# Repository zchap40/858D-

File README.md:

# 858E
(Otherwise known as the 858D++)
A new design for a hot air soldering station based on the original 858D+

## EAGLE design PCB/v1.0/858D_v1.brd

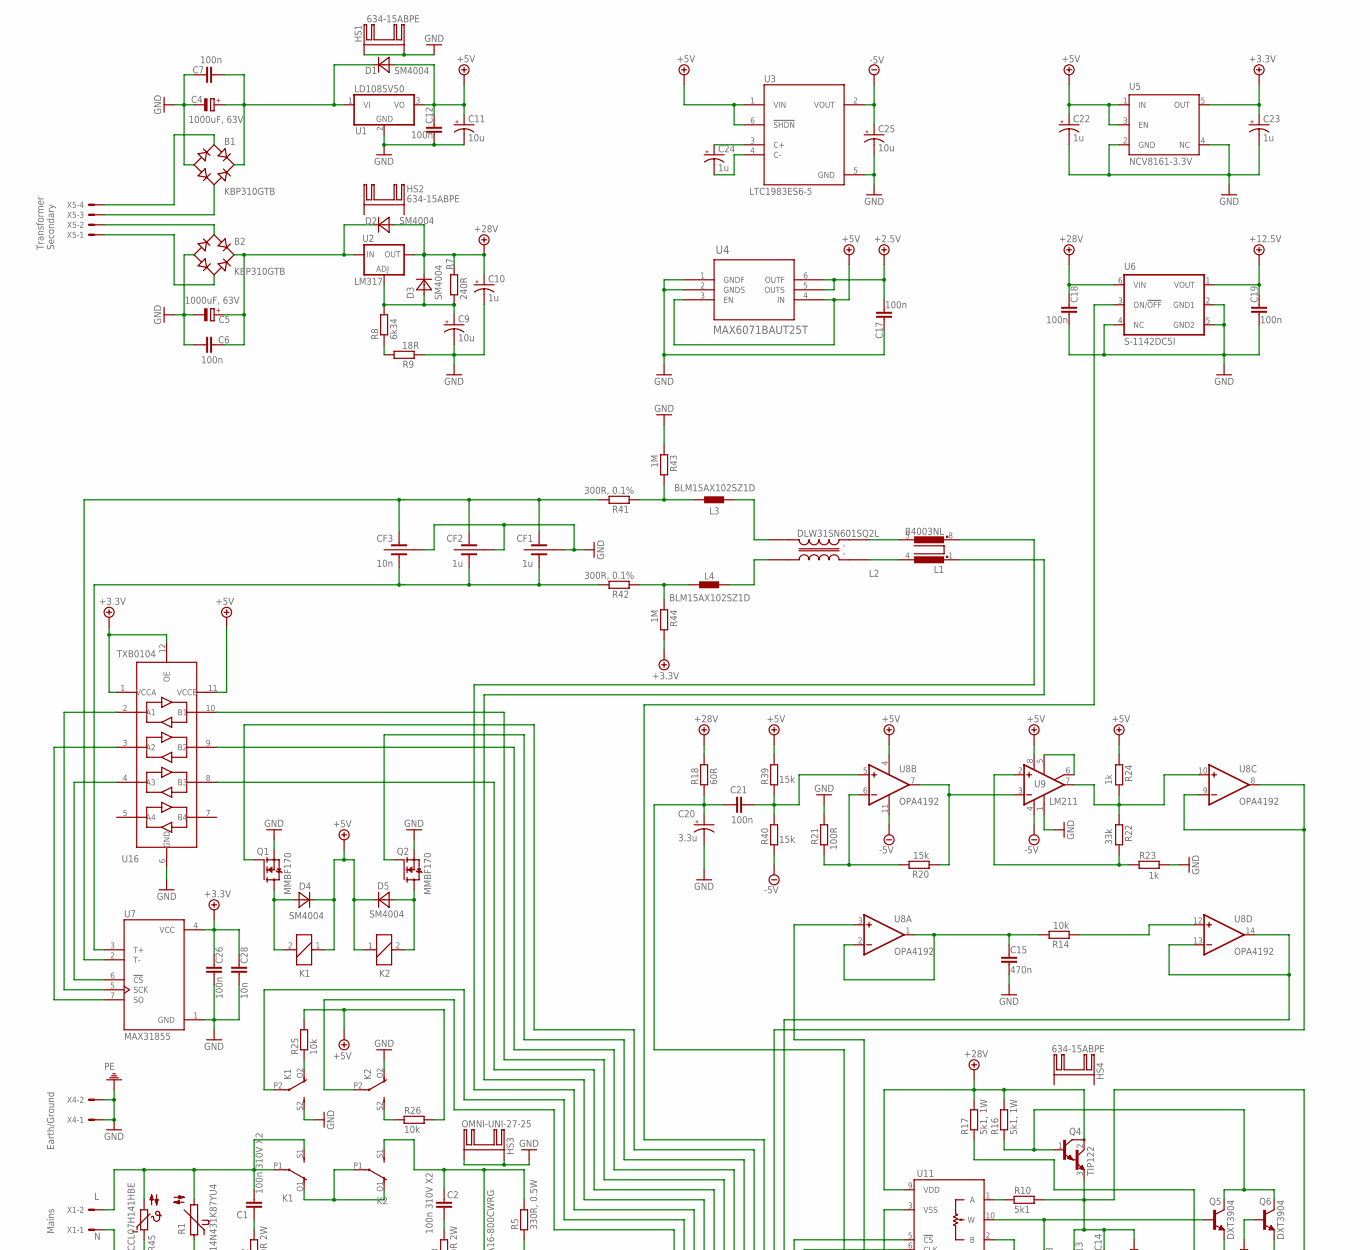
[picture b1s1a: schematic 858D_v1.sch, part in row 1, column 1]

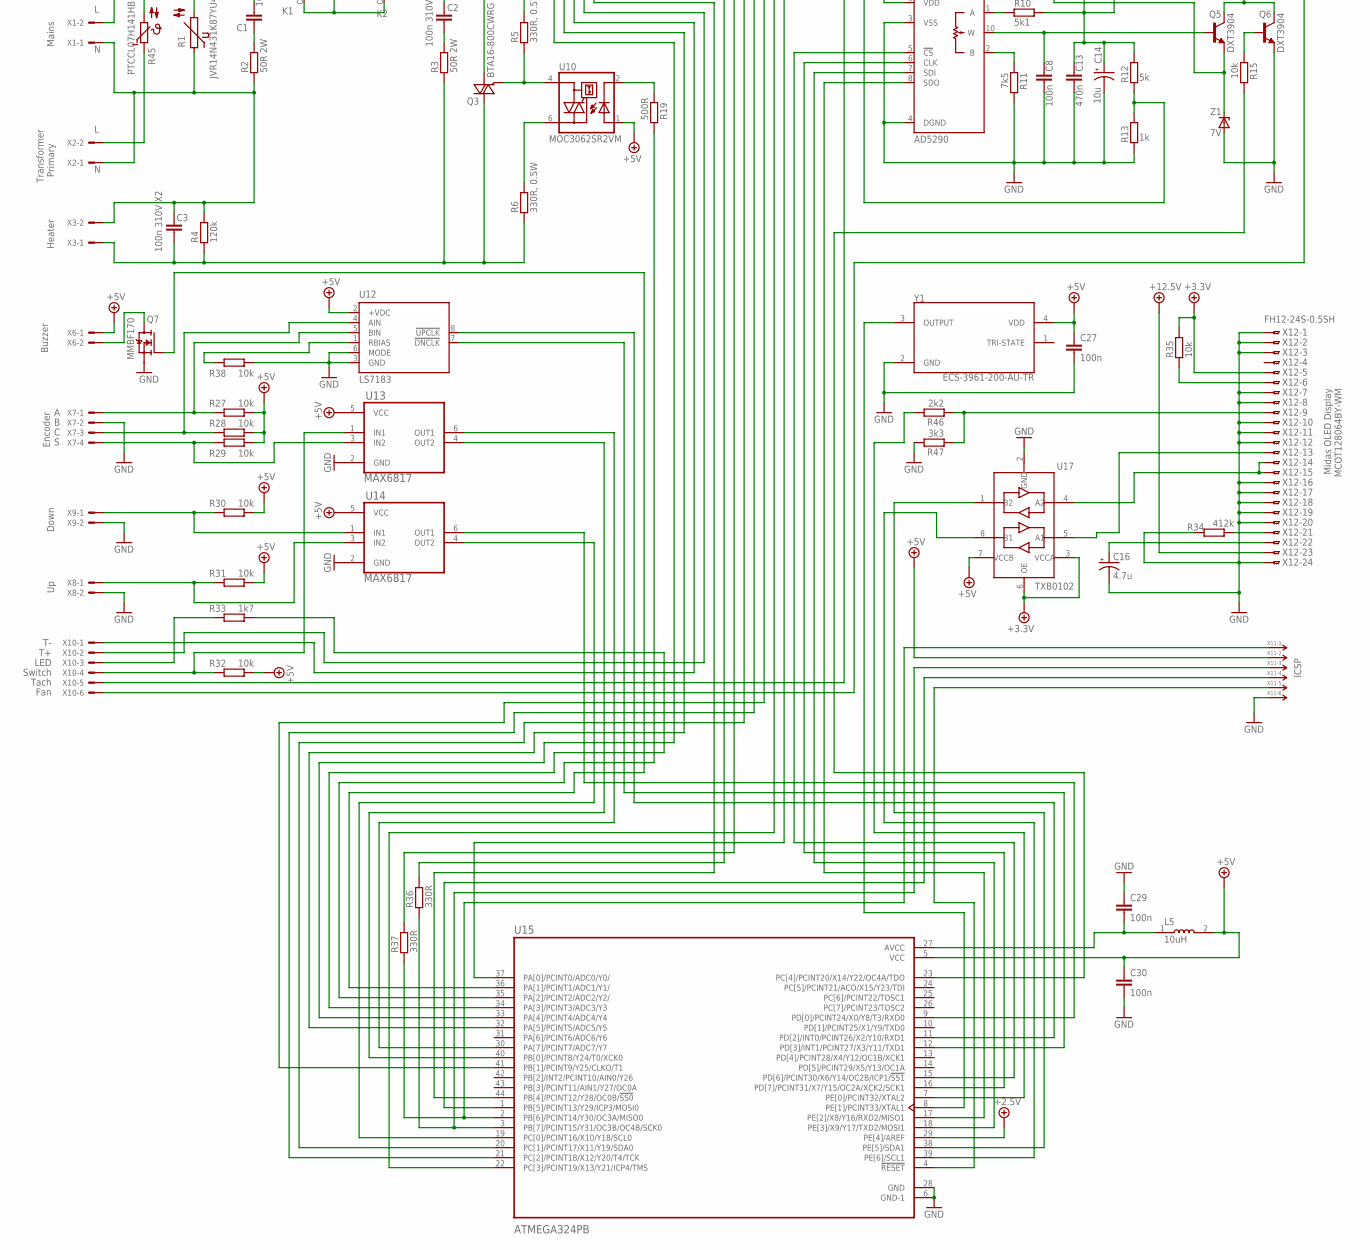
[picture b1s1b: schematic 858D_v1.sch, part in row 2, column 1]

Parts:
B1, B2: KBP310GTB; 2KBP
C1, C2, C3: 100n 310V X2; C10B6
C4, C5: 1000uF, 63V; E5-13
C6, C7, C8, C12, C17, C18, C19, C21, C26, C27, C29, C30: 100n; C1206
C9, C11, C14, C25: 10u; CT7343
C10, C22, C23, C24: 1u; B/3528-21W
C13, C15: 470n; C1206
C16: 4.7u; B/3528-21W
C20: 3.3u; B/3528-21W
C28: 10n; C0603
CF1, CF2: 1u; C1206-X2Y
CF3: 10n; C0603-X2Y
D1, D2, D3, D4, D5: SM4004; SOD123FL
HS1, HS2, HS4: 634-15ABPE
HS3: OMNI-UNI-27-25
K1, K2: 4052; F4052
L1: B4003NL; SMD-VERTICAL
L2: DLW31SN601SQ2L; FIL_DLW31SN900SQ2L
L3, L4: BLM15AX102SZ1D; 0402
L5: 10uH; INDC1608X95N
Q1, Q2, Q7: MMBF170; SOT23
Q3: BTA16-800CWRG; TO220BV
Q4: TIP122; TO220V
Q5, Q6: DXT3904; SOT89-BCE
R1: JVR14N431K87YU4; S14K11
R2, R3: 50R 2W; P0613V
R4: 120k; 0207/10
R5, R6: 330R, 0.5W; R0805
R7: 240R; R0603
R8: 6k34; R0603
R9: 18R; R0603
R10: 5k1; R0402
R11: 7k5; R0603
R12: 5k; R0402
R13, R23, R24: 1k; R0402
R14, R15, R25, R26, R27, R28, R29, R30, R31, R32, R35, R38: 10k; R0402
R16, R17: 5k1, 1W; 0411V
R18: 60R; R0805
R19: 500R; R0402
R20, R39, R40: 15k; R0402
R21: 100R; R0402
R22: 33k; R0402
R33: 1k7; R0603
R34: 412k; R0603
R36, R37: 330R; R0402
R41, R42: 300R, 0.1%; R0603
R43, R44: 1M; R0402
R45: PTCCL07H141HBE; B57164
R46: 2k2; R0402
R47: 3k3; R0402
U1: LD1085V50; TO220V
U2: LM317; 317TS
U3: LTC1983ES6-5; SOT95P280X100-6N
U4: MAX6071BAUT25T; 21-0058I
U5: NCV8161-3.3V; SOT23-DBV
U6: S-1142DC5I; HSOP-6
U7: MAX31855; SOIC127P600X175-8N
U8: OPA4192; SO14
U9: LM211; SO08
U10: MOC3062SR2VM; DIL6-SMD
U11: AD5290; MSOP10
U12: LS7183; SOIC08
U13, U14: MAX6817; SOT95P280X145-6N
U15: ATMEGA324PB; QFP80P1200X1200X120-44N
U16: TXB0104; QFN40P170X200X50-12N
U17: TXB0102; 8-VFSOP
X1, X2, X3, X4: KK-156-2
X5: KK-156-4
X6, X8, X9: 22-23-2021
X7: 22-23-2041
X10: 22-23-2061
X11: 87758-06_S; 87758-06
X12: FH12-24S-0.5SH
Y1: ECS-3961-200-AU-TR; OSC_ECS-3961-200-AU-TR
Z1: 7V; MICROSMF

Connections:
10AC1: B1.AC2, X5.3
10AC2: B1.AC1, X5.4
10DC: B1.+, C4.+, C7.2, D1.C, U1.1 (VI)
28AC1: B2.AC2, X5.1
28AC2: B2.AC1, X5.2
28DC: B2.+, C5.+, C6.2, D2.C, U2.3 (IN)
+2.5V: C17.2, U4.5 (OUTS), U4.6 (OUTF), U15.29 (PE[4]/AREF)
+3.3V: C23.+, C26.1, C28.1, R35.1, R44.2, U5.5 (OUT), U7.4 (VCC), U16.1 (VCCA), U16.12 (OE), U17.3 (VCCA), U17.6 (OE), X12.5
+5V: C11.+, C12.1, C22.+, C27.1, C30.1, D1.A, D4.C, D5.C, K1.1, K2.1, L5.2, R24.1, R25.2, R26.1, R27.2, R28.2, R29.2, R30.2, R31.2, R32.2, R39.1, U1.3 (VO), U3.1 (VIN), U3.6 (!SHDN), U4.3 (EN), U4.4 (IN), U5.1 (IN), U5.3 (EN), U8.4 (V+), U9.8 (V+), U10.1 (A), U12.2 (+VDC), U13.5 (VCC), U14.5 (VCC), U15.5 (VCC), U16.11 (VCCB), U17.7 (VCCB), X6.1, X11.2, Y1.4 (VDD)
+12.5V: C19.1, U6.1 (VOUT), X12.23
+28V: C10.+, C18.1, D2.A, D3.C, Q4.2 (C), R7.2, R16.2, R17.2, R18.2, U2.2 (OUT), U6.6 (VIN), U11.9 (VDD)
-5V: C25.+, R40.2, U3.2 (VOUT), U8.11 (V-), U9.4 (V-)
FAN: C13.1, C14.+, Q4.3 (E), R10.1, R12.1, X10.6
GND: B1.-, B2.-, C4.-, C5.-, C6.1, C7.1, C8.2, C9.-, C10.-, C11.-, C12.2, C13.2, C14.-, C15.2, C16.-, C17.1, C18.2, C19.2, C20.-, C22.-, C23.-, C25.-, C26.2, C27.2, C28.2, C29.1, C30.2, CF1.3, CF2.3, CF3.3, HS1.A2,2, HS1.B2,2, HS3.A2,2, HS3.B2,2, K1.S2 (S), K2.O2 (O), Q1.2 (S), Q2.2 (S), Q6.E, Q7.2 (S), R9.1, R11.2, R13.2, R21.2, R23.2, R34.2, R38.2, R43.1, R47.1, U1.2 (GND), U3.5 (GND), U4.1 (GNDF), U4.2 (GNDS), U5.2 (GND), U5.4 (NC), U6.2 (GND1), U6.4 (NC), U6.5 (GND2), U7.1 (GND), U9.1 (GND), U11.3 (VSS), U11.4 (DGND), U12.3 (GND), U12.6 (MODE), U13.2 (GND), U14.2 (GND), U15.6 (GND-1), U15.28 (GND), U16.6 (GND), U17.2 (GND), X4.1, X4.2, X7.2, X8.2, X9.2, X11.6, X12.1, X12.2, X12.3, X12.7, X12.8, X12.10, X12.11, X12.12, X12.16, X12.17, X12.18, X12.19, X12.20, X12.24, Y1.2 (GND), Z1.A
HOUT: C3.1, Q3.T2 (A2), R3.1, R4.1, R6.1, X3.1
L: C1.2, K1.P1, K1.S1 (S), R1.2, R45.2, X1.2
unnamed: Q4.1 (B), Q5.C, Q5.C@1 (C), Q6.C, Q6.C@1 (C), R16.1
unnamed: R45.1, X2.2
unnamed: R14.1, U8.12 (+IN)
unnamed: C1.1, R2.2
unnamed: C2.1, R3.2
unnamed: R6.2, U10.6 (A2)
unnamed: U17.4 (A2), X12.14, X12.15
unnamed: Q3.G, R5.1, U10.4 (A1)
unnamed: U7.7 (SO), U16.3 (A2)
unnamed: U7.5 (SCK), U16.2 (A1)
unnamed: U17.5 (A1), X12.13
unnamed: U7.6 (!CS), U16.4 (A3)
unnamed: U15.44 (PB[4]/PCINT12/Y28/OC0B/!SS0), U16.8 (B3)
unnamed: C8.1, Q5.B, U11.10 (W)
unnamed: R11.1, U11.2 (B)
unnamed: D4.A, K1.2, Q1.3 (D)
unnamed: C9.+, D3.A, R7.1, R8.2, U2.1 (ADJ)
unnamed: R8.1, R9.2
unnamed: D5.A, K2.2, Q2.3 (D)
unnamed: R10.2, U11.1 (A)
unnamed: Q5.E, R17.1, Z1.C
unnamed: L1.8 (3), X10.1
unnamed: Q6.B, R15.1
unnamed: L1.1, X10.2
unnamed: R36.2, U16.10 (B1)
unnamed: R37.2, U16.9 (B2)
unnamed: U6.3 (ON/!OFF), U15.41 (PB[1]/PCINT9/Y25/CLKO/T1)
unnamed: R34.1, X12.21
unnamed: R12.2, R13.1, U8.3 (+IN)
unnamed: U9.5 (ON), U9.6 (ON/STR)
unnamed: C15.1, R14.2, U8.1 (OUT), U8.2 (-IN)
unnamed: U8.13 (-IN), U8.14 (OUT), U15.37 (PA[0]/PCINT0/ADC0/Y0/)
unnamed: R19.1, U10.2 (C)
unnamed: C20.+, C21.1, R18.1, X10.5
unnamed: R19.2, U15.35 (PA[2]/PCINT2/ADC2/Y2/)
unnamed: C21.2, R39.2, R40.1, U8.5 (+IN)
unnamed: R20.1, U8.7 (OUT), U9.3 (-IN)
unnamed: R22.1, R24.2, U8.10 (+IN), U9.7 (OUT)
unnamed: R20.2, R21.1, U8.6 (-IN)
unnamed: R22.2, R23.1, U9.2 (+IN)
unnamed: U8.8 (OUT), U8.9 (-IN), U15.22 (PC[3]/PCINT19/X13/Y21/ICP4/TMS)
unnamed: U11.5 (!CS), U15.15 (PD[6]/PCINT30/X6/Y14/OC2B/ICP1/!SS1)
unnamed: U11.6 (CLK), U15.16 (PD[7]/PCINT31/X7/Y15/OC2A/XCK2/SCK1)
unnamed: U11.7 (SDI), U15.18 (PE[3]/X9/Y17/TXD2/MOSI1)
unnamed: U11.8 (SDO), U15.17 (PE[2]/X8/Y16/RXD2/MISO1)
unnamed: Q2.1 (G), U15.20 (PC[1]/PCINT17/X11/Y19/SDA0)
unnamed: K1.O2 (O), R25.1
unnamed: Q1.1 (G), U15.21 (PC[2]/PCINT18/X12/Y20/T4/TCK)
unnamed: R15.2, U15.23 (PC[4]/PCINT20/X14/Y22/OC4A/TDO)
unnamed: K2.S2 (S), R26.2
unnamed: K2.P2, U15.33 (PA[4]/PCINT4/ADC4/Y4)
unnamed: K1.P2, U15.32 (PA[5]/PCINT5/ADC5/Y5)
unnamed: Q7.3 (D), X6.2
unnamed: Q7.1 (G), U15.36 (PA[1]/PCINT1/ADC1/Y1/)
unnamed: R29.1, U13.3 (IN2), X7.4
unnamed: R28.1, U12.4 (AIN), X7.3
unnamed: R31.1, U14.3 (IN2), X8.1
unnamed: R27.1, U12.5 (BIN), X7.1
unnamed: R30.1, U14.1 (IN1), X9.1
unnamed: C16.+, X12.22
unnamed: C24.+, U3.3 (C+)
unnamed: R32.1, U13.1 (IN1), X10.4
unnamed: C24.-, U3.4 (C-)
unnamed: R33.1, X10.3
unnamed: R37.1, U15.2 (PB[6]/PCINT14/Y30/OC3A/MISO0), X11.1
unnamed: R35.2, X12.6
unnamed: R33.2, U15.34 (PA[3]/PCINT3/ADC3/Y3)
unnamed: U12.8 (!UPCLK), U15.11 (PD[2]/INT0/PCINT26/X2/Y10/RXD1)
unnamed: U12.7 (!DNCLK), U15.12 (PD[3]/INT1/PCINT27/X3/Y11/TXD1)
unnamed: U13.6 (OUT1), U15.30 (PA[7]/PCINT7/ADC7/Y7)
unnamed: U13.4 (OUT2), U15.40 (PB[0]/PCINT8/Y24/T0/XCK0)
unnamed: U14.4 (OUT2), U15.19 (PC[0]/PCINT16/X10/Y18/SCL0)
unnamed: U14.6 (OUT1), U15.9 (PD[0]/PCINT24/X0/Y8/T3/RXD0)
unnamed: CF1.2, CF2.2, CF3.2, R42.2, U7.3 (T+)
unnamed: U15.8 (PE[1]/PCINT33/XTAL1), Y1.3 (OUTPUT)
unnamed: CF1.1, CF2.1, CF3.1, R41.2, U7.2 (T-)
unnamed: R36.1, U15.3 (PB[7]/PCINT15/Y31/OC3B/OC4B/SCK0), X11.3
unnamed: U15.1 (PB[5]/PCINT13/Y29/ICP3/MOSI0), X11.4
unnamed: U15.4 (!RESET), X11.5
unnamed: R38.1, U12.1 (RBIAS)
unnamed: L1.5 (4), L2.4
unnamed: L1.4 (2), L2.1
unnamed: L2.3, L3.2
unnamed: L2.2, L4.2
unnamed: L3.1, R41.1, R43.2
unnamed: L4.1, R42.1, R44.1
unnamed: C29.2, L5.1, U15.27 (AVCC)
unnamed: C3.2, R1.1, R2.1, R4.2, X1.1, X2.1, X3.2
RESET-I2C: R46.1, U15.7 (PE[0]/PCINT32/XTAL2)
RESET-I2C-3.3: R46.2, R47.2, X12.9
SCL-I2C: U15.39 (PE[6]/SCL1), U17.8 (B1)
SDA-I2C: U15.38 (PE[5]/SDA1), U17.1 (B2)
SL1: K1.O1 (O), K2.O1 (O), K2.P1
SL2: C2.2, K2.S1 (S), Q3.T1 (A1), R5.2

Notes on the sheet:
Transformer Primary
Mains
Heater
Earth/Ground
Buzzer
Encoder
Down
Fan
Tach
Switch
LED
Transformer Secondary
Midas OLED Display MCOT128064BY-WM
ICSP

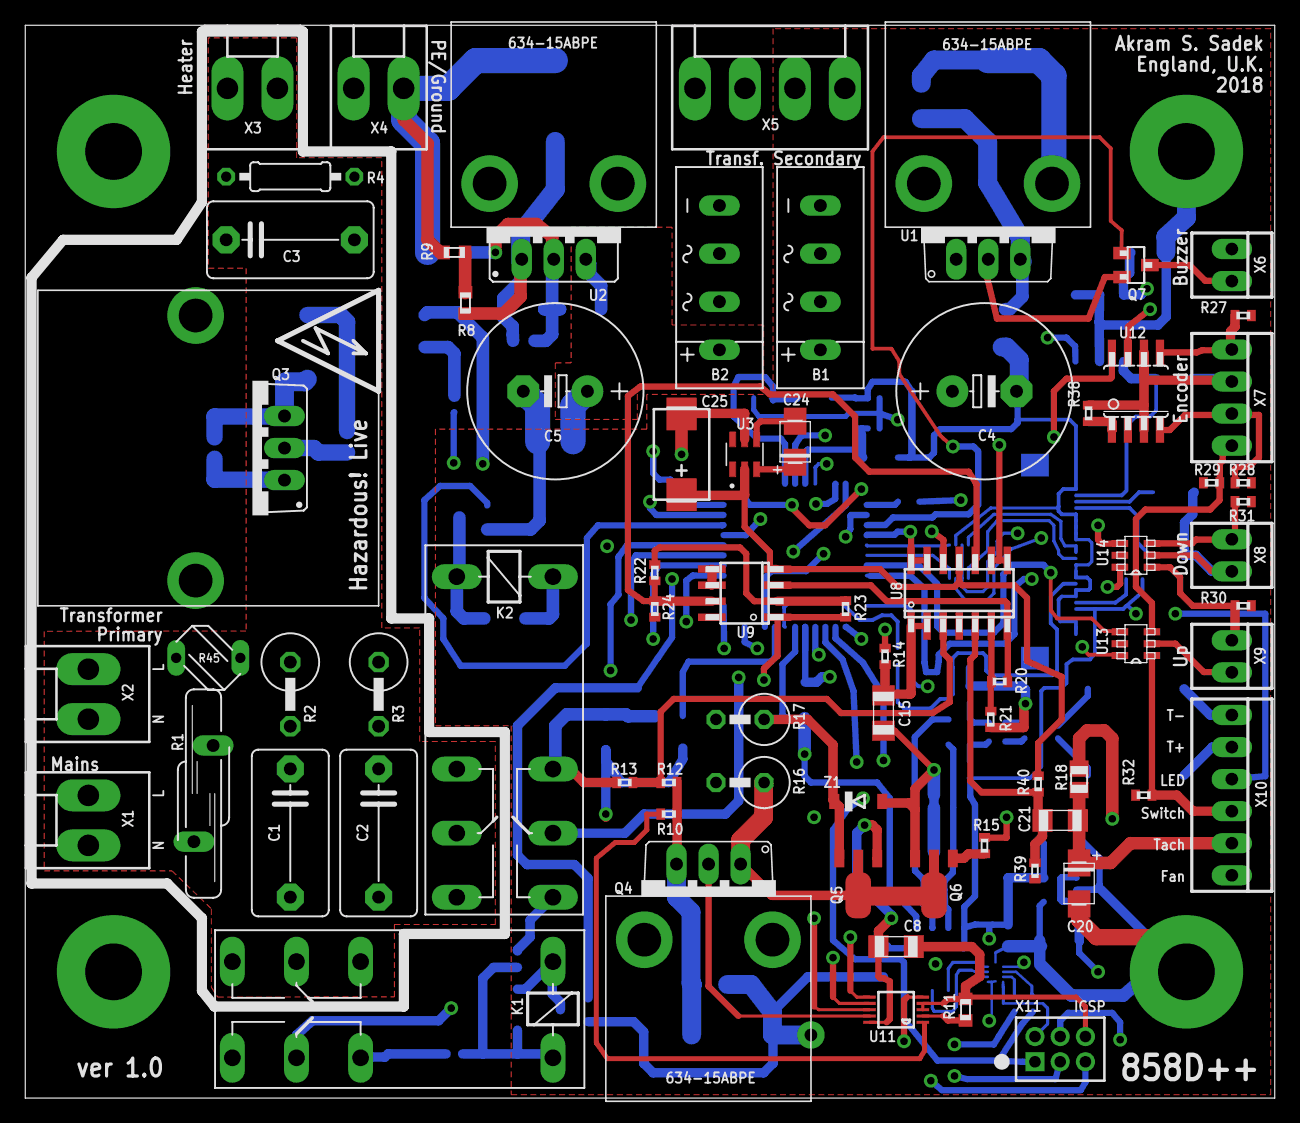
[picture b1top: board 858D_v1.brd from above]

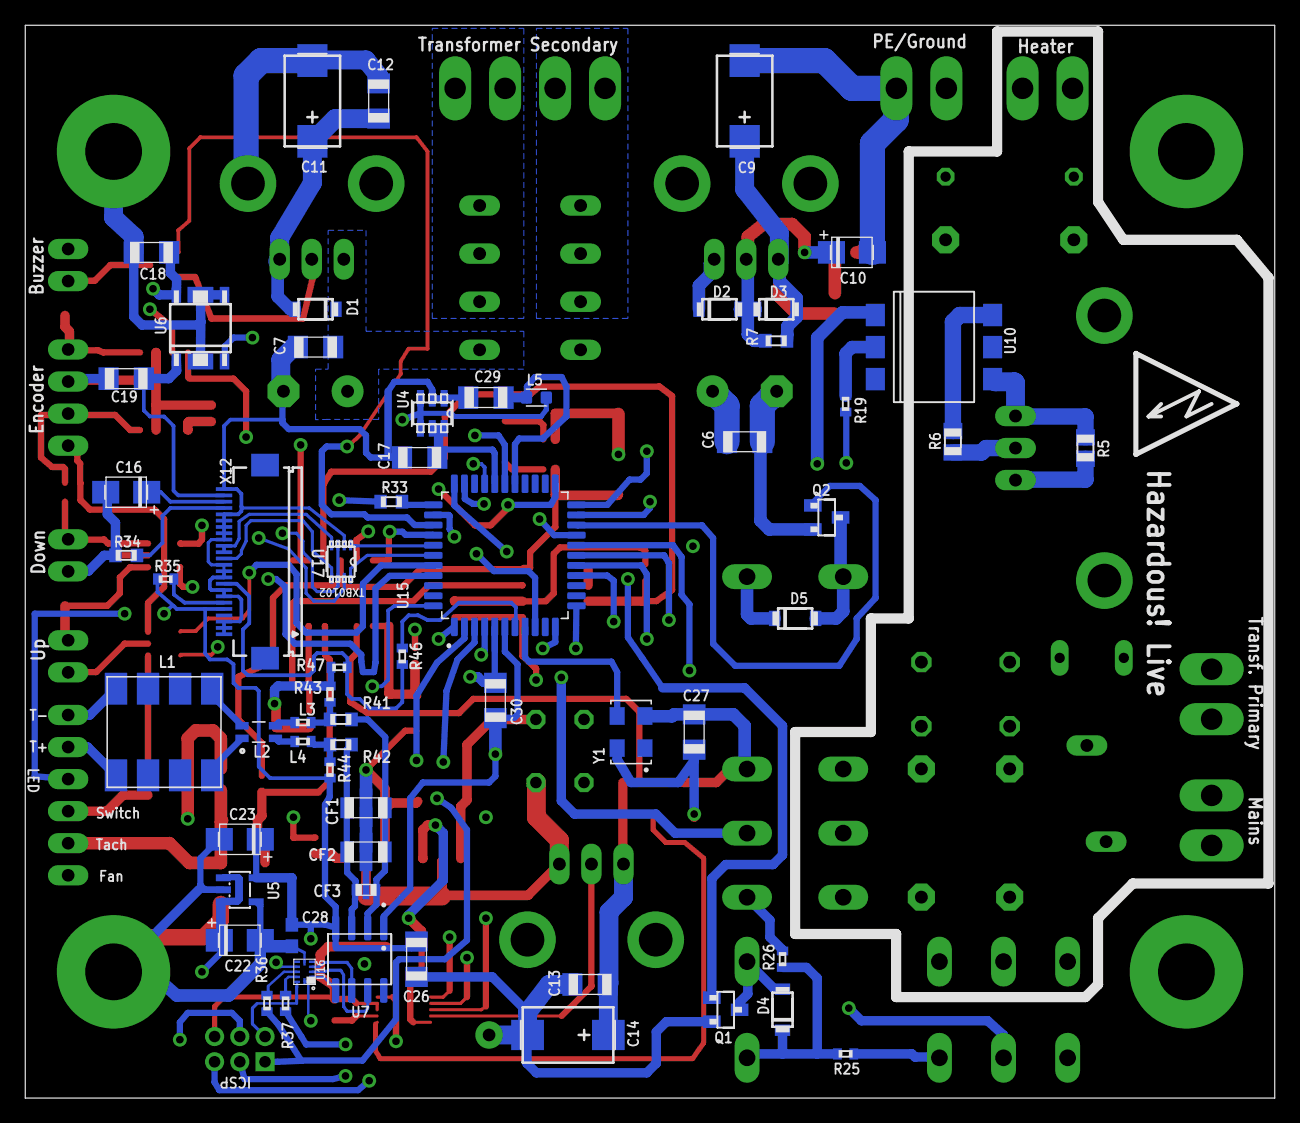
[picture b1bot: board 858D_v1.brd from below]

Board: 4 copper layers, 99.0 x 85.0 mm, 136 parts (61 on the bottom side), 110 nets.

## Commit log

2022-09-27 Uploading files to repository

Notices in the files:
parts and their libraries:
con-molex-milli-grid: Copyright (C) 2010, Bob Starr
